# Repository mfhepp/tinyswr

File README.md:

**Update 2022-10-31:** [Vojtech, OK1IAK pointed out that the circuit may increase the amount of harmonic content](https://groups.io/g/ATSprint/message/80) of your output signal. I did some preliminary analysis of this, see below for details.

**Update 2018-05-14:** [Hamshop.cz is now offering a complete kit of TinySWR](https://www.hamshop.cz/qrp-c30/tinyswr-kit-i347/), i.e. a PCB and all required parts at a very fair price (ca. 5 EUR).

**Note:** If you ordered a PCB from OSH Park before October 24, 2017, you have to fix one minor bug in the layout by means of a short piece of wire, see below for details.

# TinySWR
A tiny SWR and RF power indicator for QRP transceivers - just 20.98x14.38 mm!

This is a simple SWR and RF power indicator for QRP transceivers. It will work well with 1...5 W rigs.

The circuit is based on a design by Hans Steinort (DF3OS),
see http://www.sp5jnw.sem.pl/konstrukcje/atudf3oshtm/atudf3oseng.pdf,
with improvements from Dieter Engels (DJ6TE) and 
Hannes Hiller (DL9SCO).

I changed the values of certain components, modified the LED array, and designed a SMD PCB so that it is easier to assemble.

The PCB can be [ordered from OSH Park at a very fair price](https://oshpark.com/projects/JtKPis3T) (as of writing: USD 2.30 for three boards including shipment to Germany).

## Circuit Description ##

The schematic can be found in PDF format .

The circuit uses a standard Bruene bridge as a directional coupler, but with a resistive voltage divider (R1 - R3).

The reflected power induces a voltage at pin 3 of the coupler. Depending on that voltage, LEDs SWR 1 - 3 start to light.

Because of many variables, the LEDs do not measure the SWR in any precise way, but rather indicate whether the antenna is an acceptable match.

You can calibrate the circuit with R2 so that SWR 1 is just about to start lighting at an SWR of 1:1.

Due to the nature of the circuit, the calibration is dependent on the input power. It works best between 2.5 and 5 W but will function okay with as little as 1 W. In that case, make sure that the first LED at least glows a little bit at a near perfect SWR (like 1: 1.0...1.2) so that you will notice a mismatch.

## Part List ##
The choice of some components is critical: 
a) The LEDs have been selected to give a good indication of the SWR. Other types might work, but might be too dim to read at daylight, or the sequencial order of the LED display might stop working (e.g. SWR3 starting before SWR2).

The OSRAM LED in SMD was chosen because most standard red SMD LEDs have a higher forward voltage than THT LEDs. The footprint on the board is 0805, which is not an exact match to the OSRAM, but it will fit when handsoldering. This allows trying other SMD LEDs.

b) Small SMD trimmer potentiometers are available with many different footprints. Due to the SMD design used, you should try to get the recommended Bourns model. You could try for compatible parts from other brands; in this case, compare the footprint with that one shown in the Bourns datasheet at http://www.mouser.com/ds/2/54/314-776736.pdf. We are using the 3314G-1 (second figure).

 Id | Designator | Package | Quantity | Designation | MPN | Supplier and Reference |
--- | ---------- | ------- | -------- | ----------- | --- | ---------------------- |
1 | R1, R4 | 0805 | 2 | 820R | n/a | Any | 
2 | R2 | Bourns 3314G | 1 | 1k | Bourns 3314G-1-102E or TT Electronics 23BR1KLFTR | Mouser: 652-3314G-1-102E or 858-23BR1KLFTR; Reichelt: 23B-1,0K| 
3 | R3 | 0805 | 1 | 4.7k | n/a | Any | 
4 | R5 | 0805 | 1 | 100R | n/a | Any | 
5 | SWR1,SWR2,SWR3 | LED 1.8 or 3 mm | 3 | Red, 2mA, Forward Voltage typ 1.7, max 2.0 | KINGBRIGHT L-934LID | Reichelt: LED 3MM 2MA RT | 
6 | RF | LED 1.8 or 3 mm | 1 | Yellow, Forward Voltage typ 1.8, max 2.1 V | KINGBRIGHT L-934LYD | Reichelt: LED 3MM 2MA GE | 
7 | D1 | SMD 2115 / 0805 | 1 | Red, Forward Voltage min: 1.7, max 2.2, typ 1.8 V | OSRAM OPTO LS M67K-H2L1-1-Z  | Reichelt: LS M67K | 
8 | D2 | MiniMELF | 1 | 3.3V | n/a | Any | 
9 | D3 | MiniMELF | 1 | BAT46 | n/a | Any | 
10 | L1 | FT23 Toroid (see details) | 1 | Toroid | Amidon FT23-43 | Reichelt: FT 23-43 | 
11 | Wire 1 | n/a | 30 cm | Enameled Wire ca. 0.2 mm | n/a | Any | 
12 | Wire 2 | n/a | 5 cm | Insulated wire or enameled Wire ca. 0.5 - 0.63 mm | n/a | Any | 
13 | PCB |  |  |  |  |  | 

**Hint:** You may also want to add a few 100 R/2W resistors to you order for they will be useful as a dummy load for calibration (two in parallel -> 50R -> 1:1.0, one resistor -> 100R -> 1:2.0).

**Trimmer Potentiometer:** It seems that the following trimmer potentiometer has an identical footprint as the Bourns model and may be easier to source:

**Manufacturer:** BI Technologies, **MPN:** 23BR1KLFTR; available e.g. from 
* [Reichelt](https://www.reichelt.de/Miniaturtrimmer/23B-1-0K/3/index.html?ACTION=3&LA=3&ARTICLE=146082&GROUPID=3131&trstct=vrt_pdn)
* [Mouser](http://www.mouser.de/ProductDetail/TT-Electronics/23BR1KLFTR/)

The PCB can be [ordered from OSH Park at a very fair price](https://oshpark.com/projects/JtKPis3T) (as of writing: USD 2.30 for three boards including shipment to Germany).

Barry Gross, N1EU, took the effort to create a bill of materials at mouser.com, which will make ordering the parts much easier. His list is at
[https://www.mouser.com/ProjectManager/ProjectDetail.aspx?AccessID=7968437adc](https://www.mouser.com/ProjectManager/ProjectDetail.aspx?AccessID=7968437adc). Please note that he included multiple alternative LED brands, because the type I recommended is not available at Mouser. The list includes everything except for the PCB and the short pieces of enameled wire.

## Assembly ##
First, wind the toroid. Start with the secondary winding of N=25 turns with 0.2 mm enameled wire. Each passing of the core of the toroid counts as one turn. Make sure the turns are evenly distributed to cover ca. 270 degrees of the core. The turns in the middle (i.e. between turn 12 and 13) should be spaced a tiny bit wider than the others so that the primary turn can have tight contact with the core. Then add the one turn primary winding tightly.

**Hint:** Initially, I used enameled 0.5 mm wire for the primary winding, too, but it is pretty difficult to remove the coating at this short piece with precision. I now prefer using a short piece of insulated wire of 0.5 mm diameter or similar.

**Important:** The direction of the primary turn in relation to the secondary matters! Below is a picture that shows how it should look like.

Put the toroid aside for now.

Now, solder the SMD components except for the trimmer, starting with the resistors, then adding the MiniMELF diodes and the SMD LED on the board. The two MiniMELF diodes have a colored ring that indicates the cathode. Mind the matching "K" on the PCB. **The OSRAM SMD LED has a hardly visible cathode indicator: The respective edge is chamfered; you will need a good magnifying glass to see that.**

Then add the trimmer. Finally, add the LEDs, mind the polarity. The rectangular pads on the PCB indicate the cathode (-, shorter leg). Depending on your preferred mounting style, you may need to bend the wires of the LED in a 90 degree angle close to the LED housing; be careful to not crack the cases. Do not bend the LEDs after soldering; this may create tiny cracks that will reduce their lifespan. 

**Hint:** When you prepare the holes in the case of the rig before assembling the PCB, you can use these holes as a jig for aligning the LEDs in angle and position during soldering.

Finally, add the toroid. 

Add wires to the ANT and TX pads. I recommend to use tightly twisted wire; it will have an impedance close to 50 Ohms. You could also try short pieces of RG174 coax.

The following shows an assembled  version of the PCB (version 1.2 dated October 24, 2017):

. 

. 

Note that the orientation of several components changed in the various releases.

## Calibration ##
Connect the SWR meter to your QRP rig and attach a 50 Ohm dummy load to the ANT wires. Do use the power level you will most likely use for operating, but **not more than 5 W of power!** Now, turn the trimmer until only SWR1 continues to light a tiny little bit. Do not aim at turning it off completely, otherwise you might miss a high SWR.

**Hint:** This minimum can also be in the middle position of the trimmer potentiometer, i.e. do not expect it to be at either end of the trimming range.

If you are unable to get the other LEDs turned off, you have likely mixed the primary winding of the coupler. In that case, either swap the wires of the primary winding on the PCB, or, often easier, simply swap the ANT and TX wires.

Now you are all set! If less than two LEDs light up, your SWR should be less than 1:2. An SWR up to 1:1.3..1.5 will only light up the first LED. The brightness depends on the input power, unfortunately.

## Required Modifications on V1.1 PCB ##

There is a minor bug in version 1.1 (2017-09-14) of the PCB that has been available via OSH Park from September 14 through October 24, 2017: The connection between the ground of antenna and rig on one hand and the SWR circuit is missing. Adding a short wire from the ANT GND (the rectangular pads) to any of the other pins that should carry GND (e.g. GND side of R3, R4, R5; cathode pins of SWR3 or RF1, or anode of D3) should do the trick.

The recommended way to fix this is a short wire from ANT GND to the rectangular pad of the yellow LED labeled RF1. The picture below shows this modification. Be careful not to shorten the "RIG" GND pin with the RIG signal pin.

## Potential Risk of Additional Harmonic Content

Since the LEDs consume energy from the RF signal in a non-linear fashion, they may increase the amount of harmonic content in your transmitted signal. The full discussion is [here](https://groups.io/g/ATSprint/message/460); in a nutshell:

- the exact effect depends on the LEDs, SWR, power level, frequency, and more;
- it mostly affects the uneven harmonics, most relevant is the 3rd harmonic;
- the effect can be up to +5dB for the 3rd harmonic; that should normally not be a real problem, since a good transceiver will have them deep in the -60dB region, so even +5dB will not bring them above the required attenuation.

If you want to be on the safe side, check our transmitted signal after the installation of the TinySWR circuit with a spectrum analyzer. 

An alternative is Vojtech's [BlinkySWR](https://github.com/bubnikv/BlinkySWR), which takes extra measures for miniming the underlying effect (and operates in a digital fashion).

## Sources ##
The files in the repository contain 
* Gerber and drill files for producing your own PCBs, and
* a KiCad project with the schematics, PCB, and parts and footprints libraries.

KiCad is a great and free electronics design package. For more information, see [http://kicad.org/](http://kicad.org/).

## Acknowledments ##
The schematic is based on the design by Hans Steinort (DF3OS),
see http://www.sp5jnw.sem.pl/konstrukcje/atudf3oshtm/atudf3oseng.pdf,
with improvements from Dieter Engels (DJ6TE) and 
Hannes Hiller (DL9SCO). Thanks a lot!

## Disclaimer ##
THE DESIGN AND SOFTWARE IS PROVIDED "AS IS", WITHOUT WARRANTY OF ANY KIND, EXPRESS OR IMPLIED, INCLUDING BUT NOT LIMITED TO THE WARRANTIES OF MERCHANTABILITY, FITNESS FOR A PARTICULAR PURPOSE AND NONINFRINGEMENT. IN NO EVENT SHALL THE AUTHORS OR COPYRIGHT HOLDERS BE LIABLE FOR ANY CLAIM, DAMAGES OR OTHER LIABILITY, WHETHER IN AN ACTION OF CONTRACT, TORT OR OTHERWISE, ARISING FROM, OUT OF OR IN CONNECTION WITH THE DESIGN OR SOFTWARE OR THE USE OR OTHER DEALINGS IN THE DESIGN OR SOFTWARE.

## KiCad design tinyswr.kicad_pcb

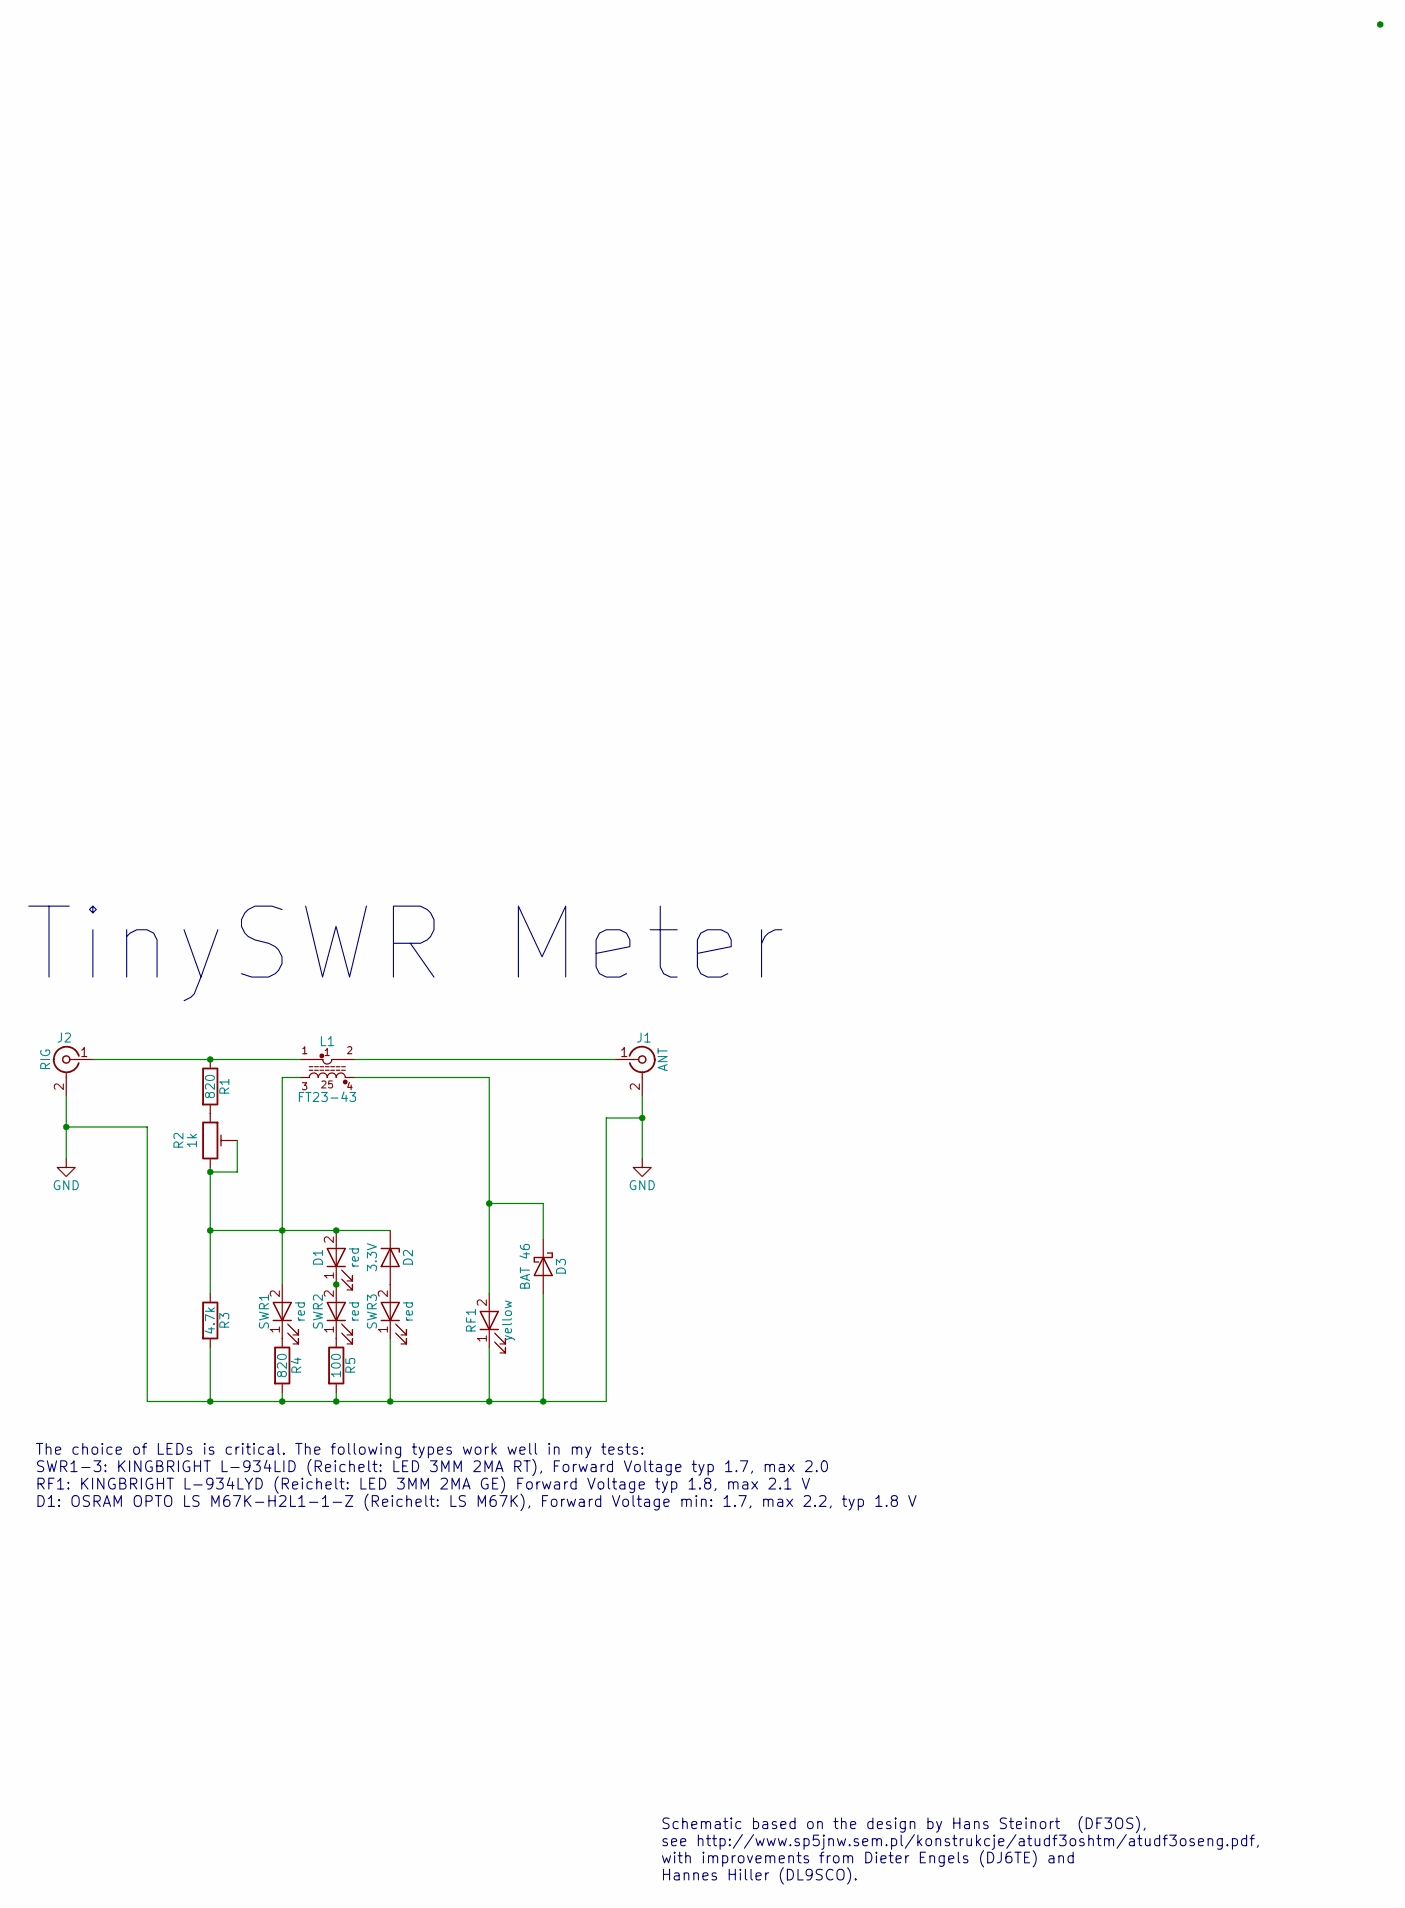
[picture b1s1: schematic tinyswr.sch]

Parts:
D1: red; LED_0805_HandSoldering
D2: 3.3V; D_MiniMELF
D3: BAT 46; D_MiniMELF
J1: ANT; BNC
J2: RIG; BNC
L1: FT23-43; FT23_horizontal
R1, R4: 820; R_0805_HandSoldering
R2: 1k; Potentiometer_Trimmer_Bourns_3314G; MPN 3314G-1-102E; Mouser Part Number 652-3314G-1-102E
R3: 4.7k; R_0805_HandSoldering
R5: 100; R_0805_HandSoldering
RF1: yellow; LED_D1.8mm_W1.8mm_H2.4mm_Horizontal_O1.27mm_Z1.6mm
SWR1, SWR2, SWR3: red; LED_D1.8mm_W1.8mm_H2.4mm_Horizontal_O1.27mm_Z1.6mm

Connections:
GND: D3.2 (A), J1.2 (Ext), J2.2 (Ext), R3.2, R4.2, R5.2, RF1.1 (K), SWR3.1 (K)
unnamed: D1.1 (K), SWR2.2 (A)
unnamed: D1.2 (A), D2.1 (K), L1.3 (2-1), R2.2, R2.3, R3.1, SWR1.2 (A)
unnamed: D2.2 (A), SWR3.2 (A)
unnamed: D3.1 (K), L1.4 (2_2), RF1.2 (A)
unnamed: J1.1 (In), L1.2 (1-2)
unnamed: J2.1 (In), L1.1 (1-1), R1.1
unnamed: R1.2, R2.1
unnamed: R4.1, SWR1.1 (K)
unnamed: R5.1, SWR2.1 (K)

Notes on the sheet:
TinySWR Meter
Schematic based on the design by Hans Steinort (DF3OS), see http://www.sp5jnw.sem.pl/konstrukcje/atudf3oshtm/atudf3oseng.pdf, with improvements from Dieter Engels (DJ6TE) and Hannes Hiller (DL9SCO).
The choice of LEDs is critical. The following types work well in my tests: SWR1-3: KINGBRIGHT L-934LID (Reichelt: LED 3MM 2MA RT), Forward Voltage typ 1.7, max 2.0 RF1: KINGBRIGHT L-934LYD (Reichelt: LED 3MM 2MA GE) Forward Voltage typ 1.8, max 2.1 V D1: OSRAM OPTO LS M67K-H2L1-1-Z (Reichelt: LS M6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

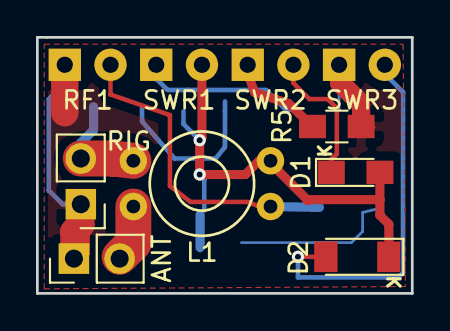
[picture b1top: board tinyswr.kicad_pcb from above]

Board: 2 copper layers, 20.8 x 14.2 mm, 15 parts (0 on the bottom side), 10 nets.

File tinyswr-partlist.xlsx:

Id | Designator | Package | Quantity | Designation | MPN | Supplier and Reference | URL
1 | R1, R4 | 0805 | 2 | 820R | n/a | Any
2 | R2 | Bourns 3314G | 1 | 1k | Bourns 3314G-1-102E | Mouser: 652-3314G-1-102E | http://www.mouser.de/ProductDetail/Bourns/3314G-1-102E/
3 | R3 | 0805 | 1 | 4.7k | n/a | Any
4 | R5 | 0805 | 1 | 100R | n/a | Any
5 | SWR1,SWR2,SWR3 | LED 1.8 or 3 mm | 3 | Red, 2mA, Forward Voltage typ 1.7, max 2.0 | KINGBRIGHT L-934LID | Reichelt: LED 3MM 2MA RT
6 | RF | LED 1.8 or 3 mm | 1 | Yellow, Forward Voltage typ 1.8, max 2.1 V | KINGBRIGHT L-934LYD | Reichelt: LED 3MM 2MA GE
7 | D1 | SMD 2115 / 0805 | 1 | Red, Forward Voltage min: 1.7, max 2.2, typ 1.8 V | OSRAM OPTO LS M67K-H2L1-1-Z | Reichelt: LS M67K
8 | D2 | MiniMELF | 1 | 3.3V | n/a | Any
9 | D3 | MiniMELF | 1 | BAT46 | n/a | Any
10 | L1 | FT23 Toroid (see details) | 1 | Toroid | Amidon FT23-43 | Reichelt: FT 23-43
11 | Wire 1 | n/a | 30 cm | Enamel Wire 0.2 mm | n/a | Any
12 | Wire 2 | n/a | 5 cm | Enamel Wire 0.5 - 0.63 mm | n/a | Any
13 | PCB

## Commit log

2017-09-13 first release
2017-09-13 added missing files
2017-09-13 cleanup
2017-09-13 added images to README
2017-09-13 resized image
2017-09-13 added warning re PCB
2017-09-13 cosmetics
2017-09-13 added schematic to images and README
2017-09-13 added image
2017-09-13 fixed image
2017-09-13 added info re alternative R2
2017-09-13 polished info re R2
2017-09-13 clarified disclaimer
2017-09-13 minor fixes
2017-09-13 added link to shopping list
2017-09-13 added link to KiCad
2017-09-13 minor
2017-10-02 fixed Mouser link
2017-10-24 fixed missing gnd connection and other bugs
2017-10-24 copy-editing README
2017-10-24 updated OSH Park order link
2017-10-27 information on bugfix for v2 added
2017-10-27 reorganized README
2017-11-11 Updated to version 1.2
2017-11-11 fixed toroid photo link
2017-11-11 removed local library links
2018-05-14 Added link to hamshop.cz kit
2018-05-14 README.me
2021-11-08 Update README.md
    https://forum.kicad.info/t/warning-avoid-all-links-to-kicad-pcb-org-use-kicad-org/31521
2022-10-30 added section re harmonics
